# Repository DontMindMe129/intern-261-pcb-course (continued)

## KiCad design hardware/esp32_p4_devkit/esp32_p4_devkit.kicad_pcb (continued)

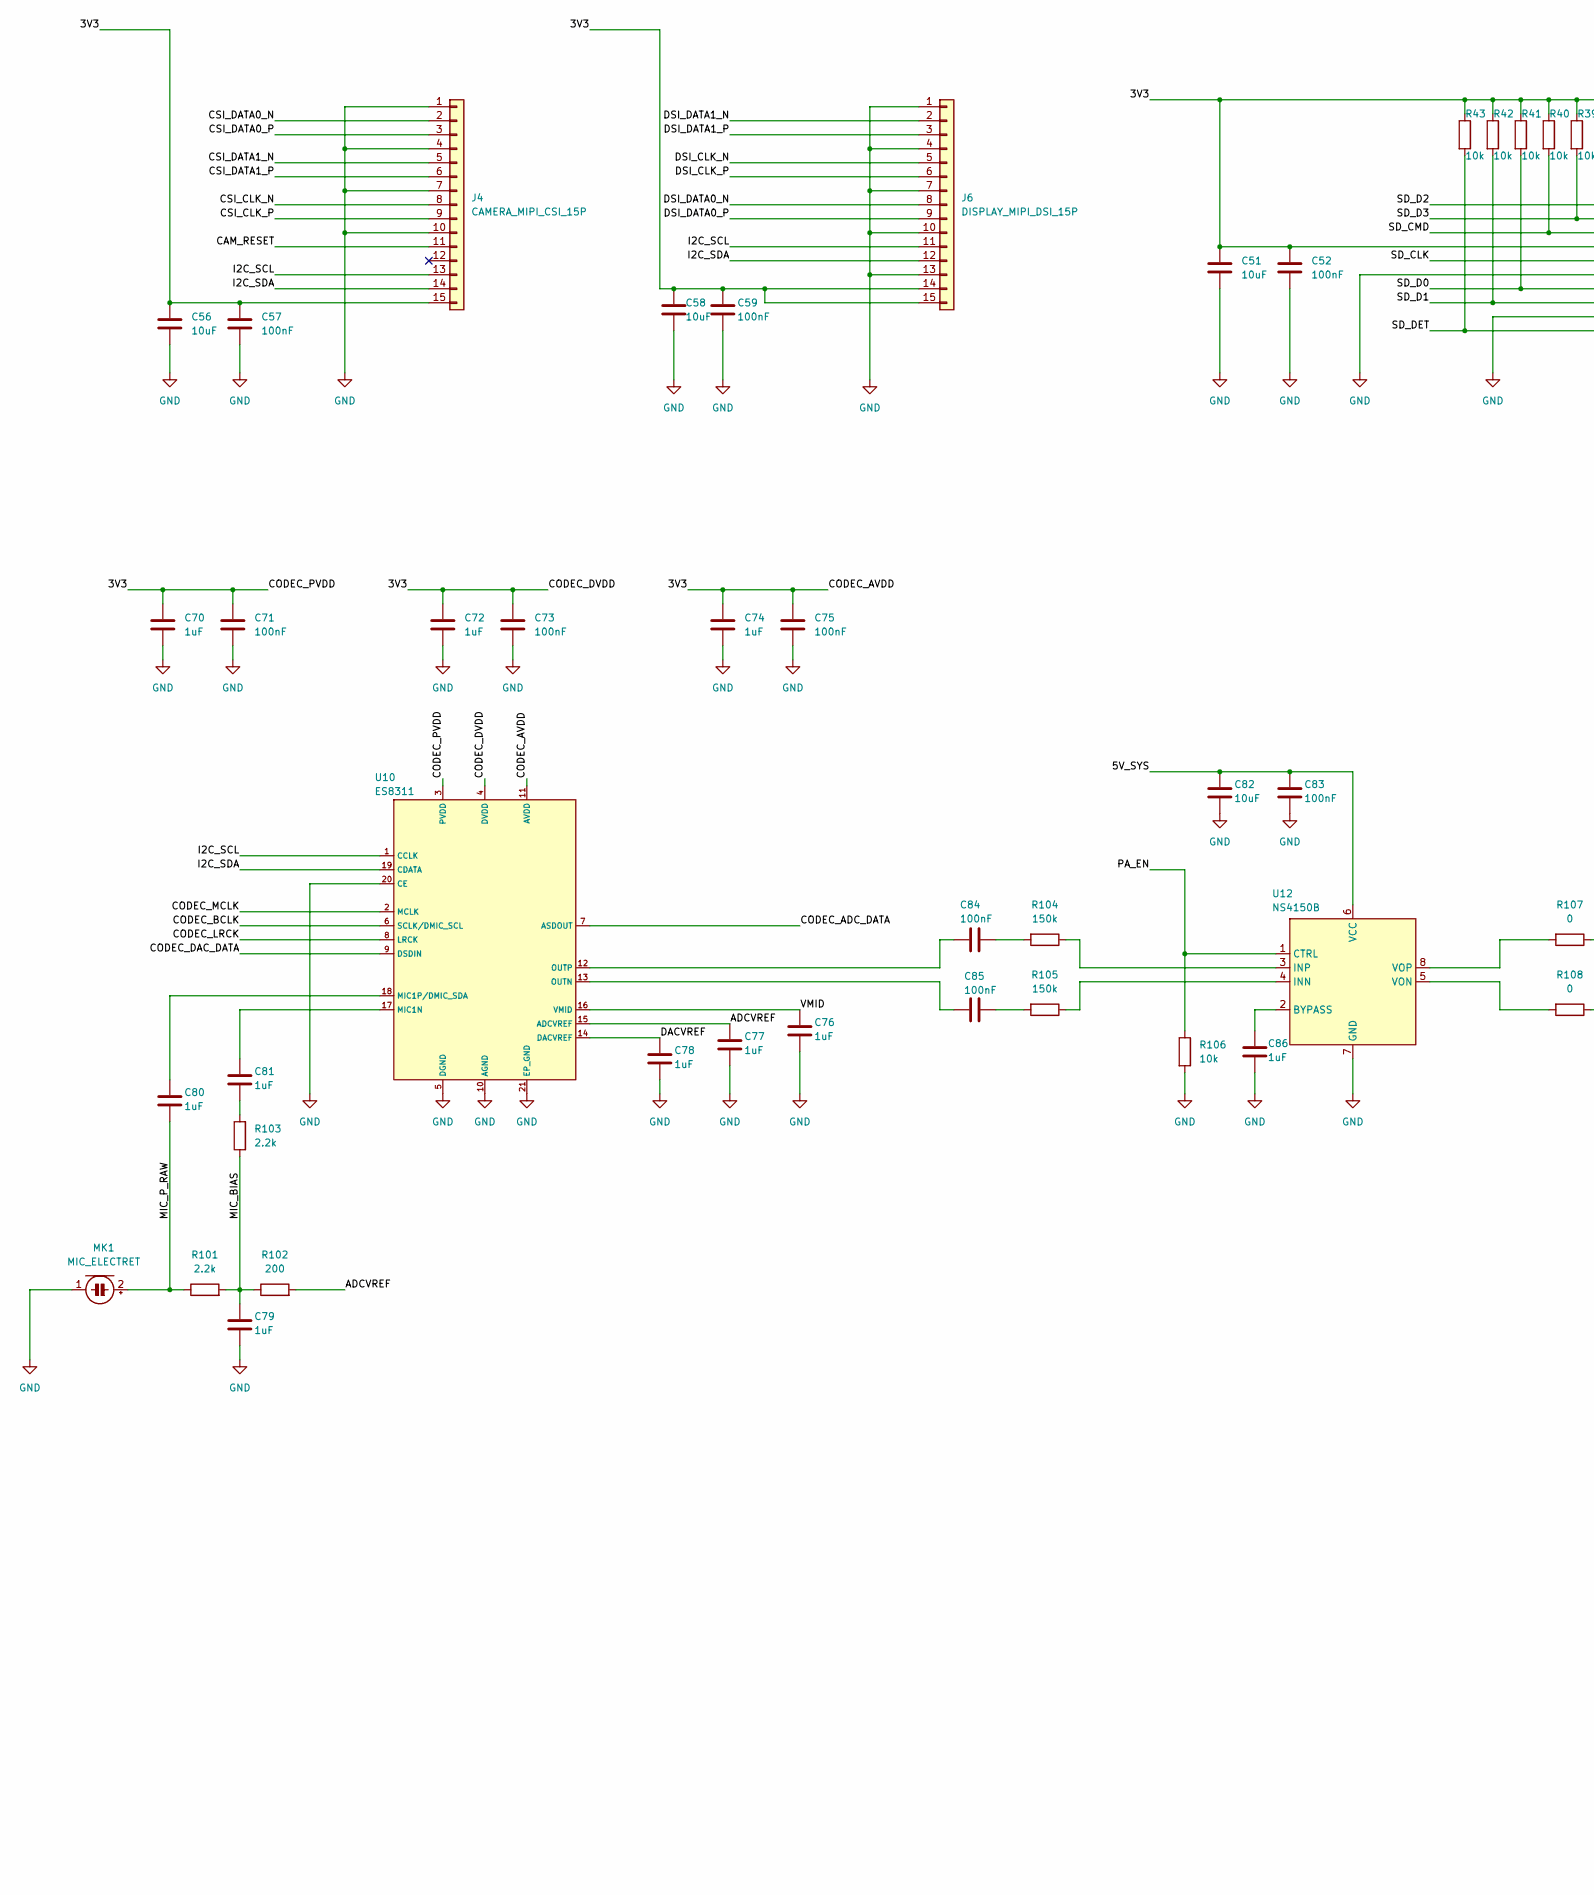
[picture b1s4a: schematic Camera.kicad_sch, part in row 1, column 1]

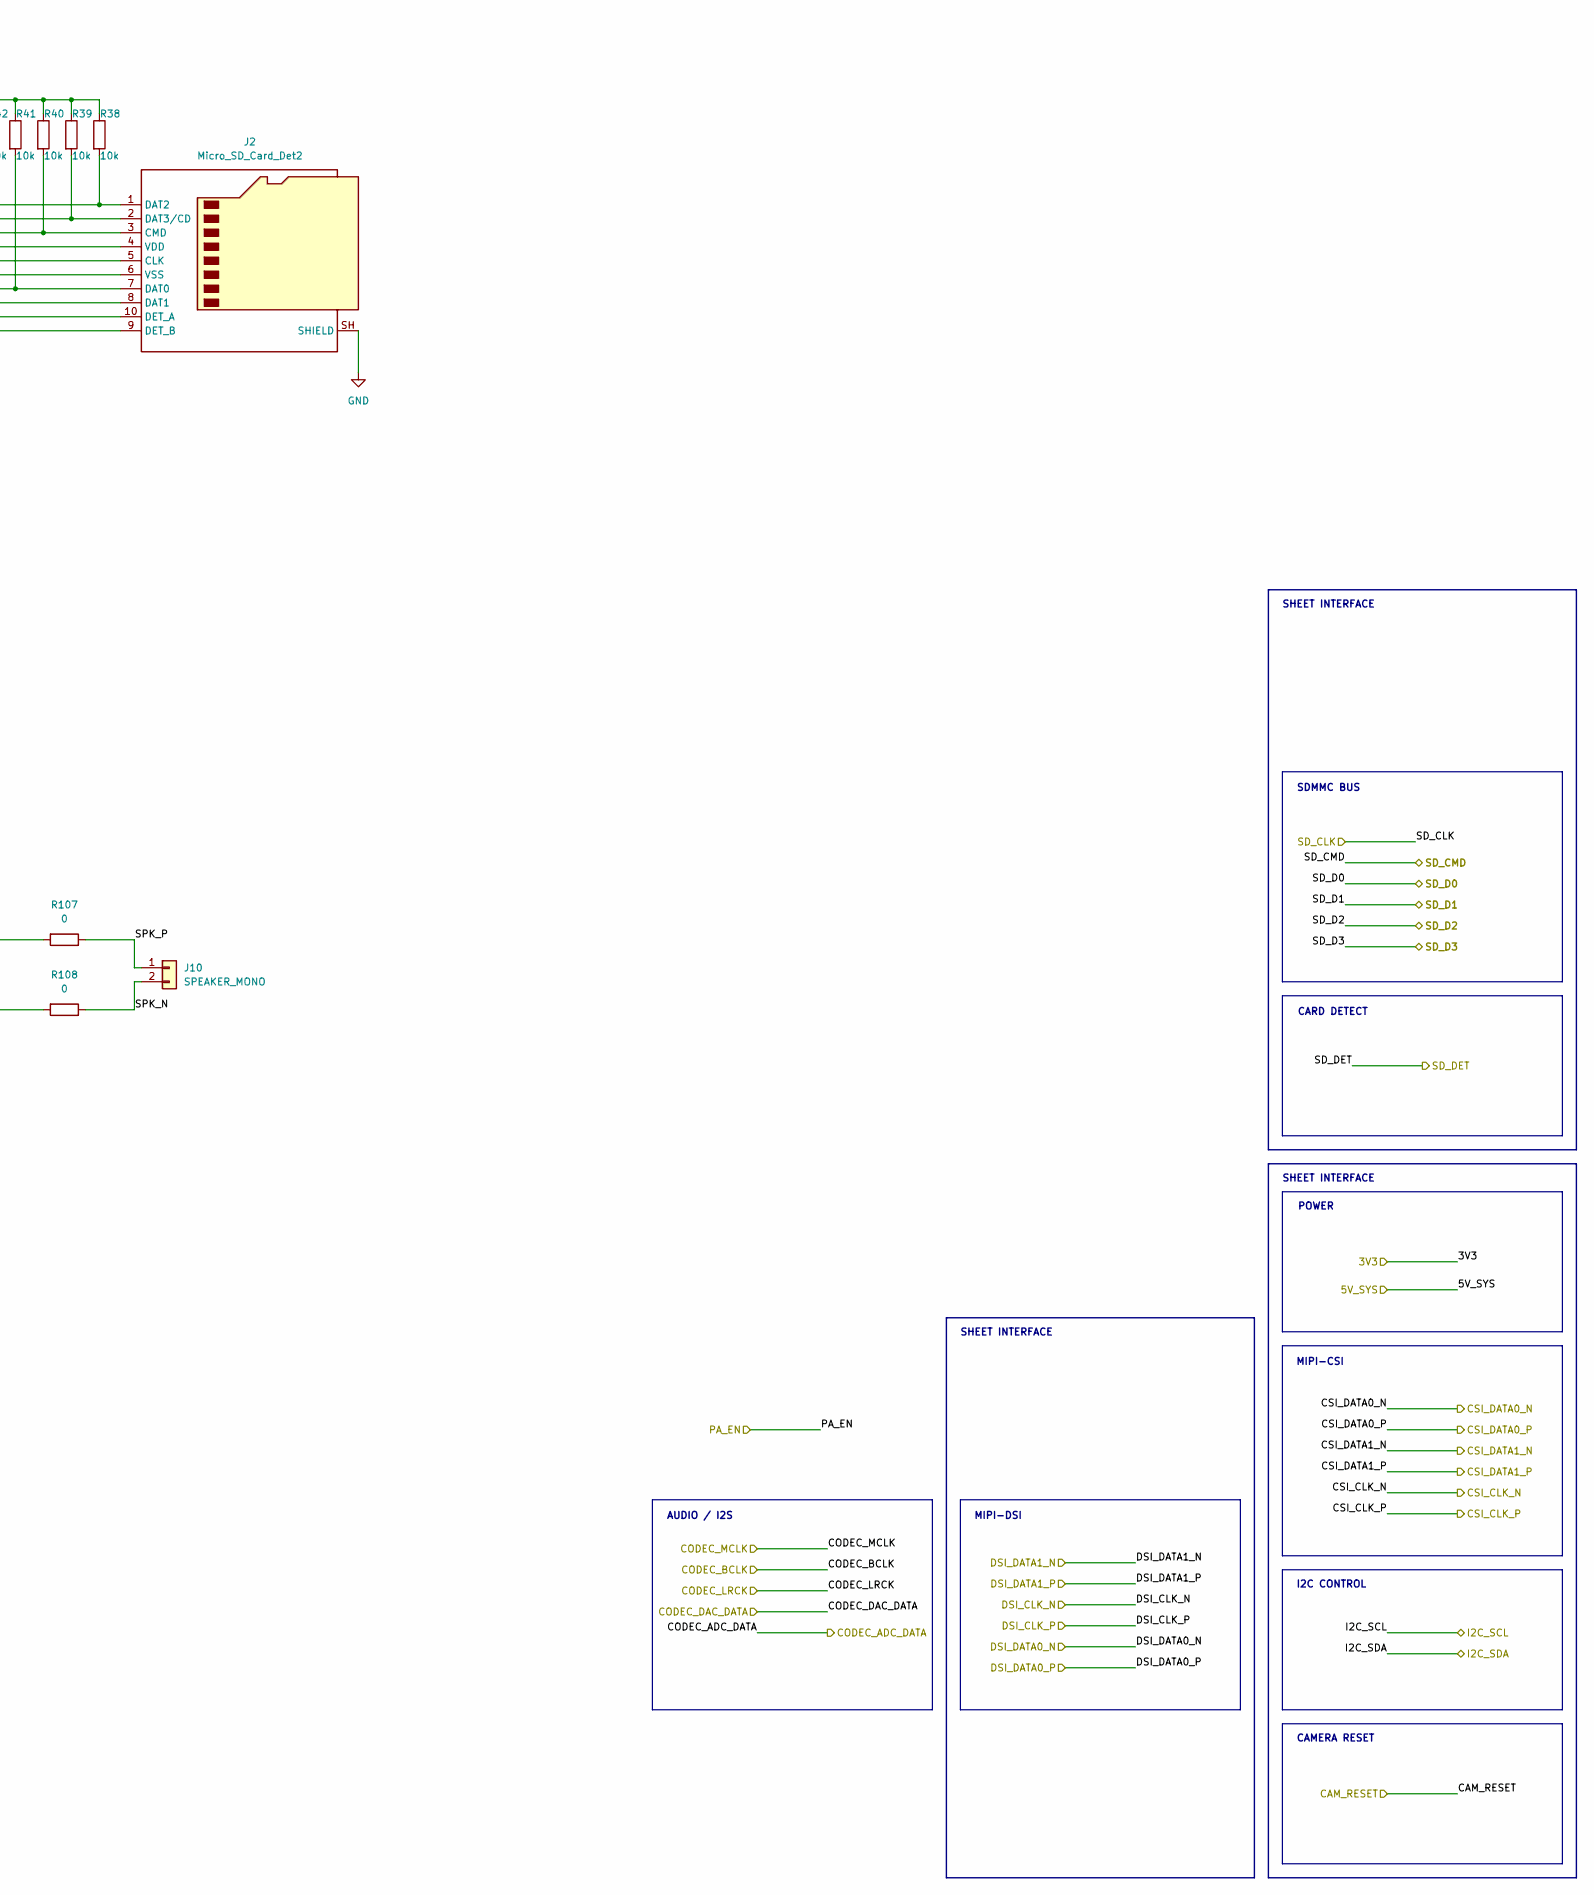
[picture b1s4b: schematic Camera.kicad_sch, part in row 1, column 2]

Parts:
C51, C56, C58, C82: 10uF; C_1206_3216Metric; MPN GRM31CR71E106MA12L
C52, C57, C59, C71, C73, C75, C83: 100nF; C_0402_1005Metric; MPN CL05B104KO5NNNC
C70, C72, C74, C76, C77, C78, C79, C80, C81, C86: 1uF; C_0805_2012Metric; MPN GRM21BR71C105KA01L
C84, C85: 100nF; C_0603_1608Metric; MPN CL10B104KB8NFNC
J2: Micro_SD_Card_Det2; microSD_HC_Hirose_DM3AT-SF-PEJM5; MPN DM3AT-SF-PEJM5
J4: CAMERA_MIPI_CSI_15P; CON15_1X15_DRB_SFW_GLE; MPN SFW15R-1STE1LF
J6: DISPLAY_MIPI_DSI_15P; CON15_1X15_DRB_SFW_GLE; MPN SFW15R-1STE1LF
J10: SPEAKER_MONO; PinHeader_1x02_P2.54mm_Vertical
MK1: MIC_ELECTRET; MIC_CMA-4544PF-W; MPN CMA-4544PF-W
R38, R39, R40, R41, R42, R43, R106: 10k; R_0603_1608Metric; MPN ERJ-3EKF1002V
R101, R103: 2.2k; R_0603_1608Metric; MPN CRCW06032K20FKEA
R102: 200; R_0603_1608Metric; MPN CRCW0603200RFKEA
R104, R105: 150k; R_0603_1608Metric; MPN CRCW0603150KFKEA
R107, R108: 0; R_0603_1608Metric; MPN ERJ-3GEY0R00V
U10: ES8311; QFN-20-1EP_3x3mm_P0.4mm_EP1.65x1.65mm; MPN ES8311
U12: NS4150B; MSOP-8_3x3mm_P0.65mm; MPN NS4150B

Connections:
/3V3: C51.1, C52.1, C56.1, C57.1, C58.1, C59.1, C70.1, C71.1, C72.1, C73.1, C74.1, C75.1, J2.4 (VDD), J4.15, J6.14, J6.15, R38.1, R39.1, R40.1, R41.1, R42.1, R43.1, U10.3 (PVDD), U10.4 (DVDD), U10.11 (AVDD); also elsewhere on the board
/5V_SYS: C82.1, C83.1, U12.6 (VCC); also elsewhere on the board
/CAM_RESET: J4.11; also elsewhere on the board
/CODEC_ADC_DATA: U10.7 (ASDOUT); also elsewhere on the board
/CODEC_BCLK: U10.6 (SCLK/DMIC_SCL); also elsewhere on the board
/CODEC_DAC_DATA: U10.9 (DSDIN); also elsewhere on the board
/CODEC_LRCK: U10.8 (LRCK); also elsewhere on the board
/CODEC_MCLK: U10.2 (MCLK); also elsewhere on the board
/CSI_CLK_N: J4.8; also elsewhere on the board
/CSI_CLK_P: J4.9; also elsewhere on the board
/CSI_DATA0_N: J4.2; also elsewhere on the board
/CSI_DATA0_P: J4.3; also elsewhere on the board
/CSI_DATA1_N: J4.5; also elsewhere on the board
/CSI_DATA1_P: J4.6; also elsewhere on the board
/DSI_CLK_N: J6.5; also elsewhere on the board
/DSI_CLK_P: J6.6; also elsewhere on the board
/DSI_DATA0_N: J6.8; also elsewhere on the board
/DSI_DATA0_P: J6.9; also elsewhere on the board
/DSI_DATA1_N: J6.2; also elsewhere on the board
/DSI_DATA1_P: J6.3; also elsewhere on the board
/I2C_SCL: J4.13, J6.11, U10.1 (CCLK); also elsewhere on the board
/I2C_SDA: J4.14, J6.12, U10.19 (CDATA); also elsewhere on the board
/Multimedia/ADCVREF: C77.1, R102.2, U10.15 (ADCVREF)
/Multimedia/DACVREF: C78.1, U10.14 (DACVREF)
/Multimedia/MIC_BIAS: C79.1, R101.2, R102.1, R103.1
/Multimedia/MIC_P_RAW: C80.2, MK1.2 (+), R101.1
/Multimedia/SPK_N: J10.2, R108.1
/Multimedia/SPK_P: J10.1, R107.1
/Multimedia/VMID: C76.1, U10.16 (VMID)
/PA_EN: R106.1, U12.1 (CTRL); also elsewhere on the board
/SD_CLK: J2.5 (CLK); also elsewhere on the board
/SD_CMD: J2.3 (CMD), R40.2; also elsewhere on the board
/SD_D0: J2.7 (DAT0), R41.2; also elsewhere on the board
/SD_D1: J2.8 (DAT1), R42.2; also elsewhere on the board
/SD_D2: J2.1 (DAT2), R38.2; also elsewhere on the board
/SD_D3: J2.2 (DAT3/CD), R39.2; also elsewhere on the board
/SD_DET: J2.9 (DET_B), R43.2; also elsewhere on the board
GND: C51.2, C52.2, C56.2, C57.2, C58.2, C59.2, C70.2, C71.2, C72.2, C73.2, C74.2, C75.2, C76.2, C77.2, C78.2, C79.2, C82.2, C83.2, C86.2, J2.6 (VSS), J2.10 (DET_A), J2.SH (SHIELD), J4.1, J4.4, J4.7, J4.10, J6.1, J6.4, J6.7, J6.10, J6.13, MK1.1 (-), R106.2, U10.5 (DGND), U10.10 (AGND), U10.20 (CE), U10.21 (EP_GND), U12.7 (GND); also elsewhere on the board
unnamed: C81.2, R103.2
unnamed: C84.2, R104.2
unnamed: C85.2, R105.2
unnamed: C81.1, U10.17 (MIC1N)
unnamed: C80.1, U10.18 (MIC1P/DMIC_SDA)
unnamed: C85.1, U10.13 (OUTN)
unnamed: C84.1, U10.12 (OUTP)
unnamed: C86.1, U12.2 (BYPASS)
unnamed: R105.1, U12.4 (INN)
unnamed: R104.1, U12.3 (INP)
unnamed: R108.2, U12.5 (VON)
unnamed: R107.2, U12.8 (VOP)

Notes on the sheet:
CARD DETECT
SHEET INTERFACE
POWER
AUDIO / I2S
SDMMC BUS
MIPI-CSI
CAMERA RESET
I2C CONTROL
MIPI-DSI

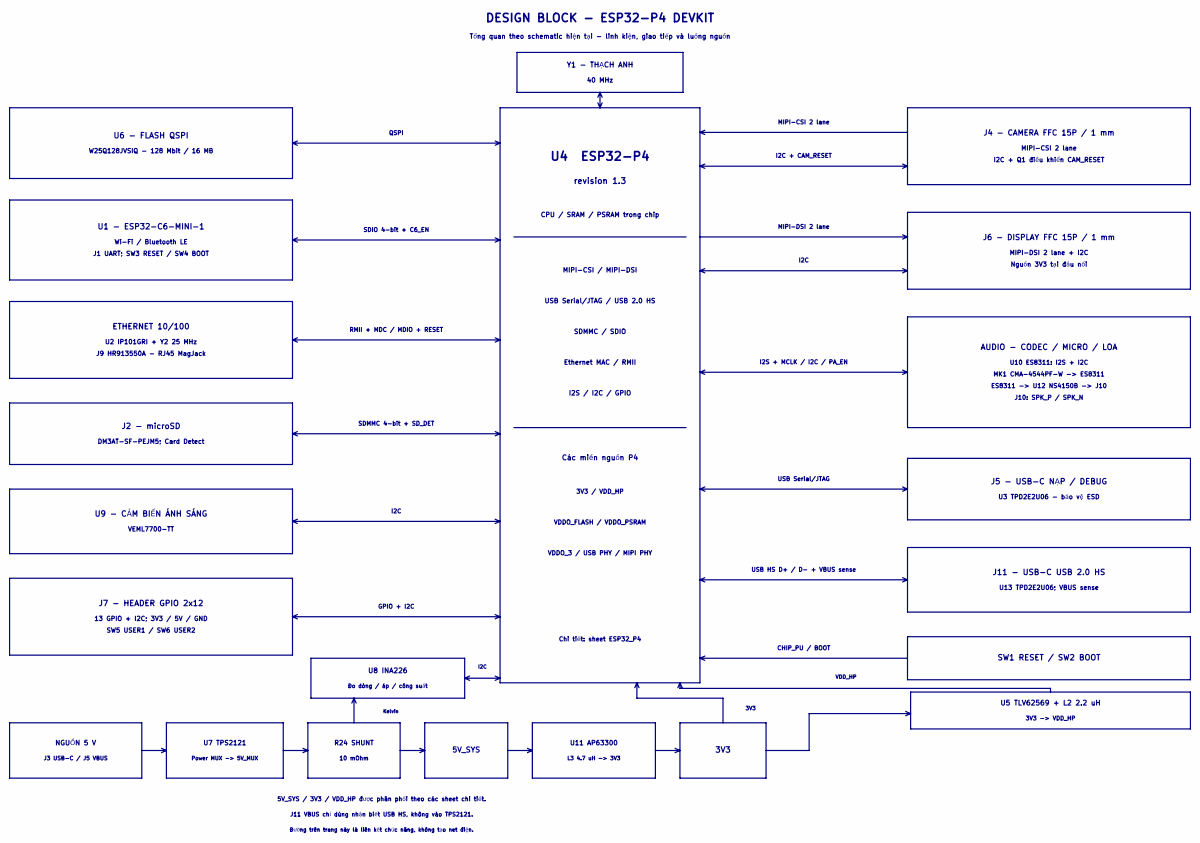
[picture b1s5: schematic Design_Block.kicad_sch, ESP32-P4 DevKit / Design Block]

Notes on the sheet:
U7 TPS2121
I2C
3V3
I2C + Q1 điều khiển CAM_RESET
3V3 / VDD_HP
Các miền nguồn P4
J11 VBUS chỉ dùng nhận biết USB HS, không vào TPS2121.
J6 - DISPLAY FFC 15P / 1 mm
VDDO_3 / USB PHY / MIPI PHY
Chi tiết: sheet ESP32_P4
L3 4.7 uH -> 3V3
J1 UART; SW3 RESET / SW4 BOOT
NGUỒN 5 V
5V_SYS
USB HS D+ / D- + VBUS sense
USB Serial/JTAG / USB 2.0 HS
VDDO_FLASH / VDDO_PSRAM
DM3AT-SF-PEJM5; Card Detect
VEML7700-TT
VDD_HP
Đo dòng / áp / công suất
Wi-Fi / Bluetooth LE
ES8311 -> U12 NS4150B -> J10
U4 ESP32-P4
U9 - CẢM BIẾN ÁNH SÁNG
U13 TPD2E2U06; VBUS sense
GPIO + I2C
U2 IP101GRI + Y2 25 MHz
SDMMC / SDIO
5V_SYS / 3V3 / VDD_HP được phân phối theo các sheet chi tiết.
SW5 USER1 / SW6 USER2
SDMMC 4-bit + SD_DET
U6 - FLASH QSPI
DESIGN BLOCK - ESP32-P4 DEVKIT
MK1 CMA-4544PF-W -> ES8311
ETHERNET 10/100
U8 INA226
MIPI-CSI 2 lane
revision 1.3
Tổng quan theo schematic hiện tại - linh kiện, giao tiếp và luồng nguồn

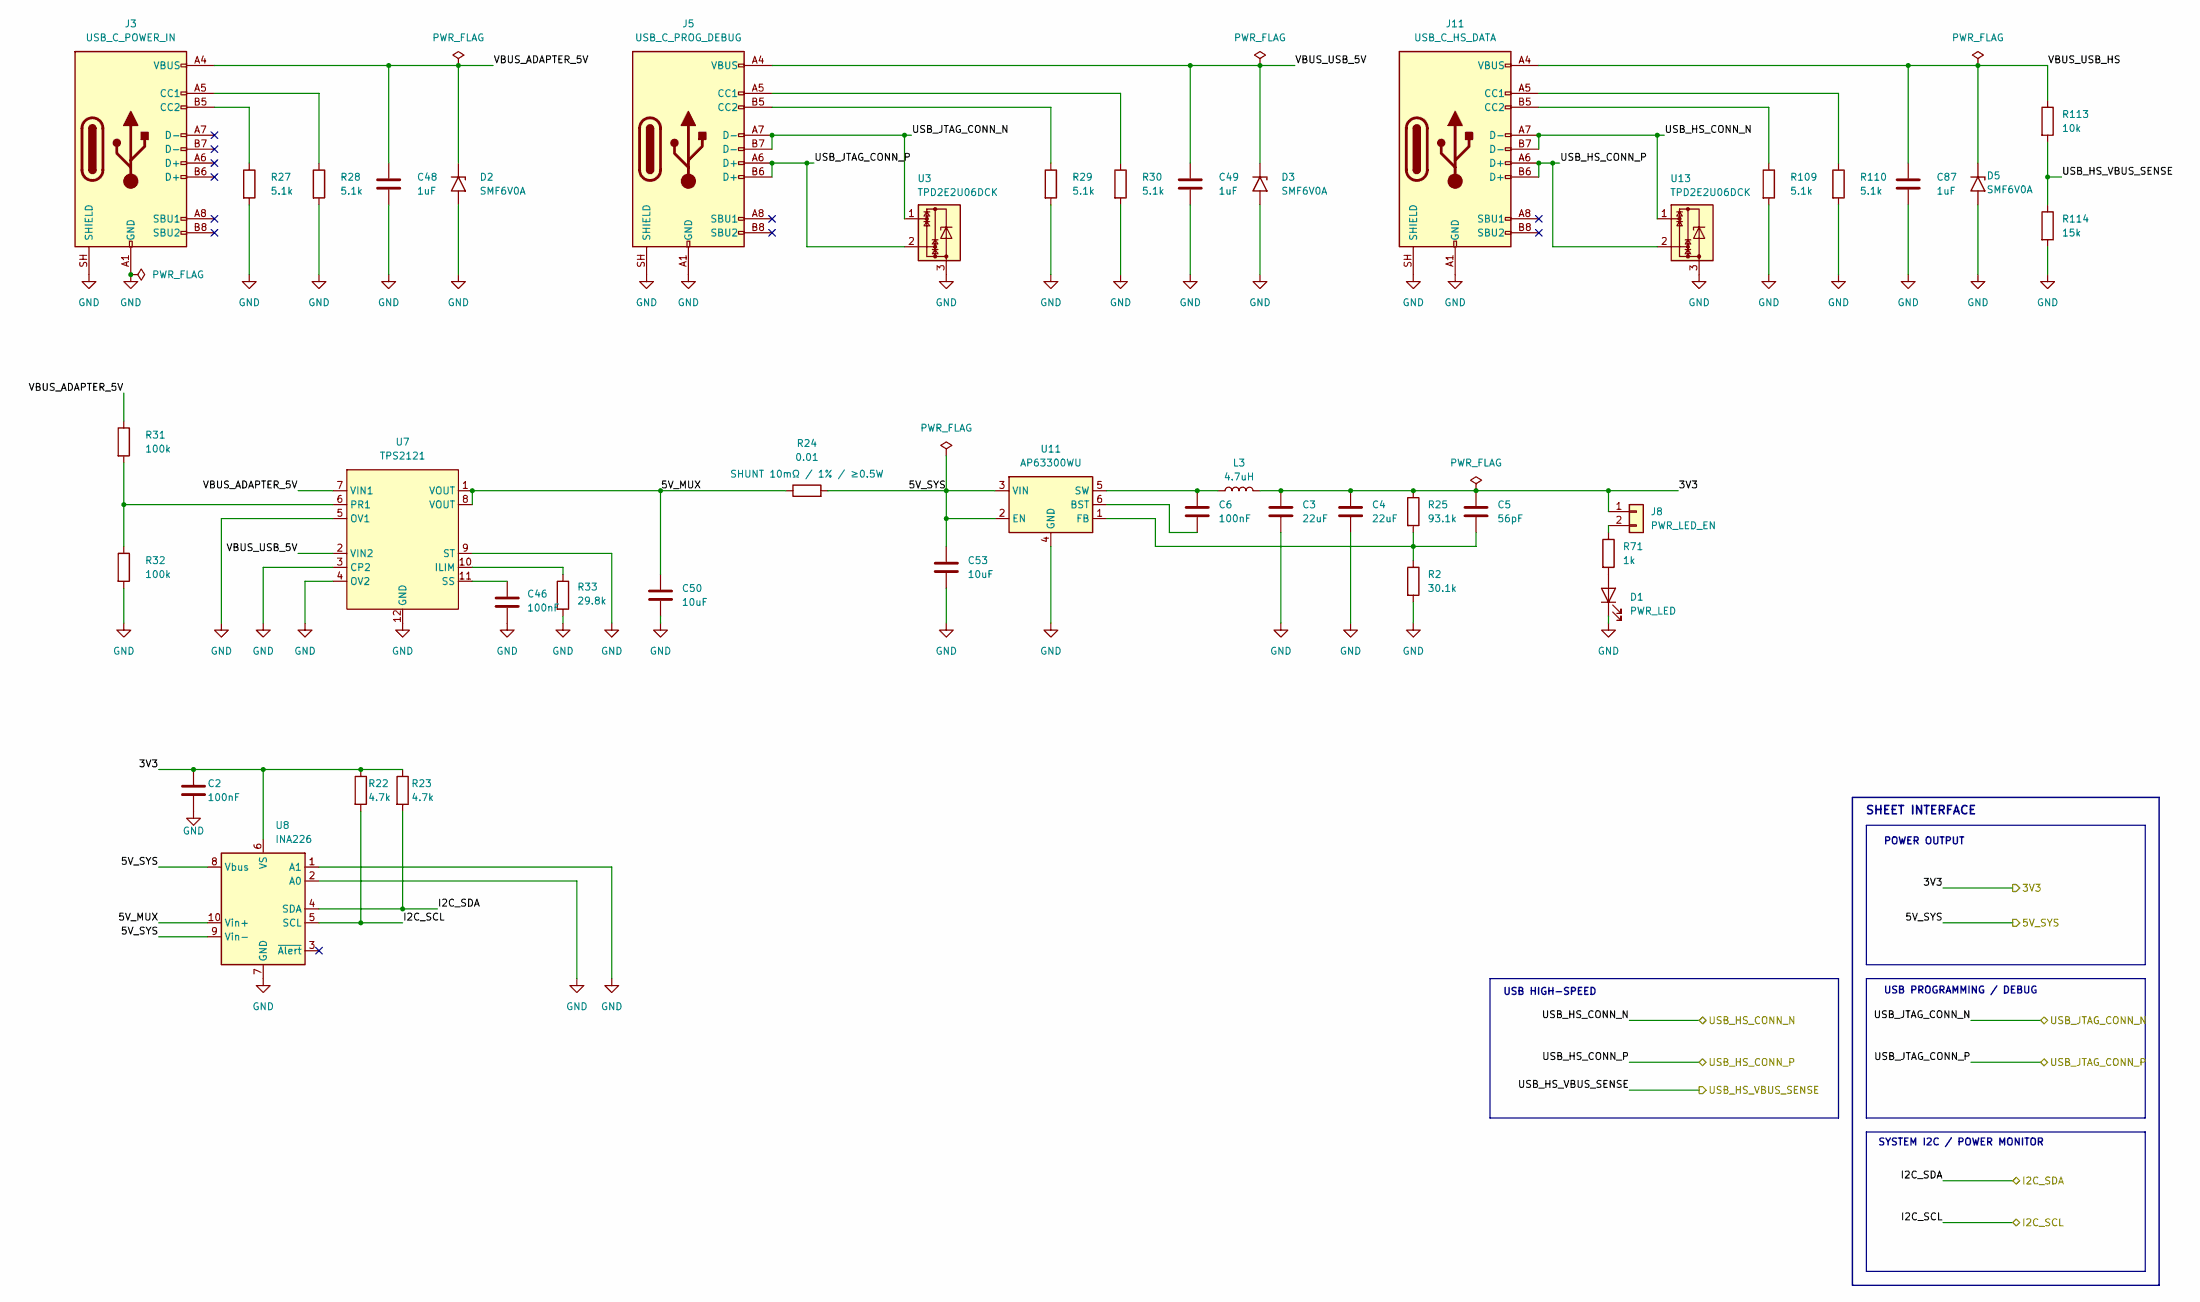
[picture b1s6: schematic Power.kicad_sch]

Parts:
C2: 100nF; C_0402_1005Metric; MPN CL05B104KO5NNNC
C3, C4: 22uF; C_1206_3216Metric; MPN CL31A226KOCLNNC
C5: 56pF; C_0603_1608Metric; MPN C0603C560J5GACTU
C6, C46: 100nF; C_0603_1608Metric; MPN CL10B104KB8NFNC
C48, C49, C87: 1uF; C_0805_2012Metric; MPN GRM21BR71C105KA01L
C50, C53: 10uF; C_1206_3216Metric; MPN GRM31CR71E106MA12L
D1: PWR_LED; LED_0603_1608Metric; MPN LTST-C190KGKT
D2, D3, D5: SMF6V0A; D_SMA; MPN SMF6V0A-M3-08
J3: USB_C_POWER_IN; USB_C_Receptacle_HRO_TYPE-C-31-M-12; MPN TYPE-C-31-M-12
J5: USB_C_PROG_DEBUG; USB_C_Receptacle_HRO_TYPE-C-31-M-12; MPN TYPE-C-31-M-12
J8: PWR_LED_EN; PinHeader_1x02_P2.54mm_Vertical; MPN TSW-102-07-G-S
J11: USB_C_HS_DATA; USB_C_Receptacle_HRO_TYPE-C-31-M-12; MPN TYPE-C-31-M-12
L3: 4.7uH; L_Abracon_ASPI-0630LR; MPN ASPI-0630LR-4R7M-T15
R2: 30.1k; R_0603_1608Metric; MPN ERA-3AEB3012V
R22, R23: 4.7k; R_0603_1608Metric; MPN ERJ-3EKF4701V
R24: 0.01; R_Shunt_Vishay_WSLP2512_10mOhm; MPN WSLP2512R0100FEA
R25: 93.1k; R_0603_1608Metric; MPN ERA-3AEB9312V
R27, R28, R29, R30, R109, R110: 5.1k; R_0603_1608Metric; MPN CRCW06035K10FKEA
R31, R32: 100k; R_0603_1608Metric; MPN CRCW0603100KFKEA
R33: 29.8k; R_0603_1608Metric; MPN RT0603BRD0729K8L
R71: 1k; R_0603_1608Metric; MPN ERJ-3EKF1001V
R113: 10k; R_0603_1608Metric; MPN ERJ-3EKF1002V
R114: 15k; R_0603_1608Metric; MPN CRCW060315K0FKEA
U3, U13: TPD2E2U06DCK; SOT-323_SC-70; MPN TPD2E2U06QDCKRQ1
U7: TPS2121; Texas_VQFN-HR-12_2x2.5mm_P0.5mm; MPN TPS2121RUXR
U8: INA226; TSSOP-10_3x3mm_P0.5mm; MPN INA226AIDGSR
U11: AP63300WU; TSOT-23-6; MPN AP63300WU-7

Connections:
/3V3: C2.1, C3.1, C4.1, C5.1, J8.1, L3.2, R22.1, R23.1, R25.1, U8.6 (VS); also elsewhere on the board
/5V_SYS: C53.1, R24.2, U8.8 (Vbus), U8.9 (Vin-), U11.2 (EN), U11.3 (VIN); also elsewhere on the board
/I2C_SCL: R22.2, U8.5 (SCL); also elsewhere on the board
/I2C_SDA: R23.2, U8.4 (SDA); also elsewhere on the board
/Power_USB/5V_MUX: C50.1, R24.1, U7.1 (VOUT), U7.8 (VOUT), U8.10 (Vin+)
/Power_USB/VBUS_ADAPTER_5V: C48.1, D2.1 (A1), J3.A4 (VBUS), J3.A9 (VBUS), J3.B4 (VBUS), J3.B9 (VBUS), R31.1, U7.7 (VIN1)
/Power_USB/VBUS_USB_5V: C49.1, D3.1 (A1), J5.A4 (VBUS), J5.A9 (VBUS), J5.B4 (VBUS), J5.B9 (VBUS), U7.2 (VIN2)
/Power_USB/VBUS_USB_HS: C87.1, D5.1 (A1), J11.A4 (VBUS), J11.A9 (VBUS), J11.B4 (VBUS), J11.B9 (VBUS), R113.1
/USB_HS_CONN_N: J11.A7 (D-), J11.B7 (D-), U13.1; also elsewhere on the board
/USB_HS_CONN_P: J11.A6 (D+), J11.B6 (D+), U13.2; also elsewhere on the board
/USB_HS_VBUS_SENSE: R113.2, R114.1; also elsewhere on the board
/USB_JTAG_CONN_N: J5.A7 (D-), J5.B7 (D-), U3.1; also elsewhere on the board
/USB_JTAG_CONN_P: J5.A6 (D+), J5.B6 (D+), U3.2; also elsewhere on the board
GND: C2.2, C3.2, C4.2, C46.2, C48.2, C49.2, C50.2, C53.2, C87.2, D1.1 (K), D2.2 (A2), D3.2 (A2), D5.2 (A2), J3.A1 (GND), J3.A12 (GND), J3.B1 (GND), J3.B12 (GND), J3.SH (SHIELD), J5.A1 (GND), J5.A12 (GND), J5.B1 (GND), J5.B12 (GND), J5.SH (SHIELD), J11.A1 (GND), J11.A12 (GND), J11.B1 (GND), J11.B12 (GND), J11.SH (SHIELD), R2.2, R27.2, R28.2, R29.2, R30.2, R32.2, R33.2, R109.2, R110.2, R114.2, U3.3, U7.3 (CP2), U7.4 (OV2), U7.5 (OV1), U7.9 (ST), U7.12 (GND), U8.1 (A1), U8.2 (A0), U8.7 (GND), U11.4 (GND), U13.3; also elsewhere on the board
unnamed: D1.2 (A), R71.2
unnamed: J3.A5 (CC1), R28.1
unnamed: J3.B5 (CC2), R27.1
unnamed: J5.A5 (CC1), R30.1
unnamed: J5.B5 (CC2), R29.1
unnamed: J8.2, R71.1
unnamed: J11.A5 (CC1), R110.1
unnamed: J11.B5 (CC2), R109.1
unnamed: R33.1, U7.10 (ILIM)
unnamed: R31.2, R32.1, U7.6 (PR1)
unnamed: C46.1, U7.11 (SS)
unnamed: C6.2, U11.6 (BST)
unnamed: C5.2, R2.1, R25.2, U11.1 (FB)
unnamed: C6.1, L3.1, U11.5 (SW)

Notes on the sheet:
SHEET INTERFACE
USB HIGH-SPEED
SYSTEM I2C / POWER MONITOR
USB PROGRAMMING / DEBUG
POWER OUTPUT
